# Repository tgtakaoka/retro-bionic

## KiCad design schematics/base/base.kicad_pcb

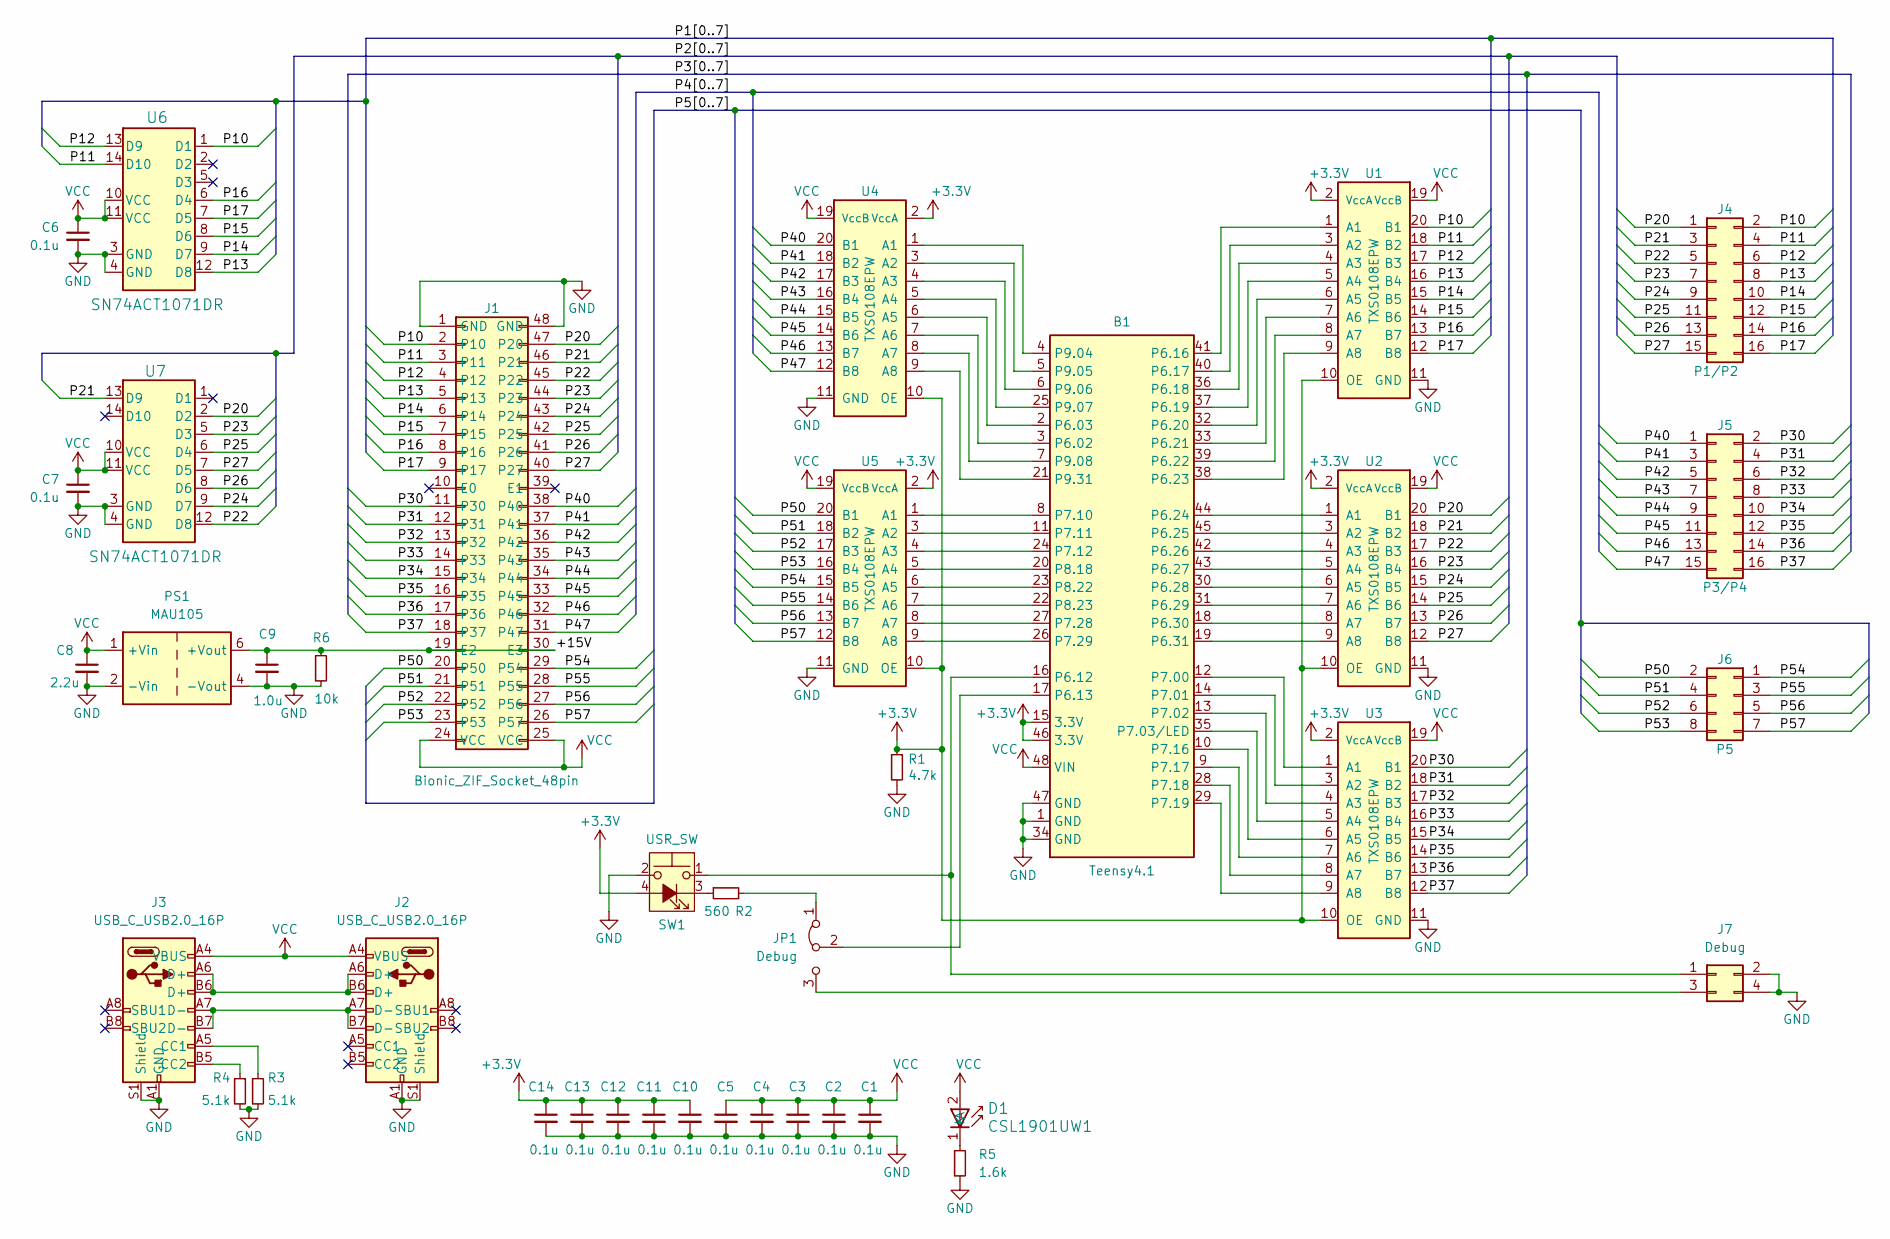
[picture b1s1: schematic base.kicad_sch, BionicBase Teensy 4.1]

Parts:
B1: Teensy4.1; Teensy 4.1
C1, C2, C3, C4, C5, C6, C7, C10, C11, C12, C13, C14: 0.1u; C_0603_1608Metric_Pad1.08x0.95mm_HandSolder
C8: 2.2u; C_0603_1608Metric_Pad1.08x0.95mm_HandSolder
C9: 1.0u; C_0603_1608Metric_Pad1.08x0.95mm_HandSolder
D1: CSL1901UW1; LED_CSL1901UW1_ROM-M
J1: Bionic_ZIF_Socket_48pin; Aries_ZIF_socket_DIP-48-pin
J2, J3: USB_C_USB2.0_16P; GCT_USB4085-GF-A_REVB
J4: P1/P2; PinHeader_2x08_P2.54mm_Horizontal
J5: P3/P4; PinHeader_2x08_P2.54mm_Horizontal
J6: P5; PinHeader_2x04_P2.54mm_Horizontal
J7: Debug; PinHeader_2x02_P2.54mm_Horizontal
JP1: Debug; PinHeader_1x03_P2.54mm_Vertical
PS1: MAU105; Converter_DCDC_Minmax_MAU100_THT
R1: 4.7k; R_0603_1608Metric_Pad0.98x0.95mm_HandSolder
R2: 560; R_0603_1608Metric_Pad0.98x0.95mm_HandSolder
R3, R4: 5.1k; R_0603_1608Metric_Pad0.98x0.95mm_HandSolder
R5: 1.6k; R_0603_1608Metric_Pad0.98x0.95mm_HandSolder
R6: 10k; R_0603_1608Metric_Pad0.98x0.95mm_HandSolder
SW1: USR_SW; SW_PUSH_LED_6mm
U1, U2, U3, U4, U5: TXS0108EPW; PW20-M
U6, U7: SN74ACT1071DR; D14-M

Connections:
+3.3V: B1.15 (3.3V), B1.46 (3.3V), C10.1, C11.1, C12.1, C13.1, C14.1, R1.1, SW1.4 (A), U1.2 (VccA), U1.10 (OE), U2.2 (VccA), U2.10 (OE), U3.2 (VccA), U3.10 (OE), U4.2 (VccA), U4.10 (OE), U5.2 (VccA), U5.10 (OE)
/+15V: C9.1, J1.19 (E2), J1.30 (E3), PS1.6 (+Vout), R6.1
/P10: J1.2 (P10), J4.2, U1.20 (B1), U6.1 (D1)
/P11: J1.3 (P11), J4.4, U1.18 (B2), U6.14 (D10)
/P12: J1.4 (P12), J4.6, U1.17 (B3), U6.13 (D9)
/P13: J1.5 (P13), J4.8, U1.16 (B4), U6.12 (D8)
/P14: J1.6 (P14), J4.10, U1.15 (B5), U6.9 (D7)
/P15: J1.7 (P15), J4.12, U1.14 (B6), U6.8 (D6)
/P16: J1.8 (P16), J4.14, U1.13 (B7), U6.6 (D4)
/P17: J1.9 (P17), J4.16, U1.12 (B8), U6.7 (D5)
/P20: J1.47 (P20), J4.1, U2.20 (B1), U7.2 (D2)
/P21: J1.46 (P21), J4.3, U2.18 (B2), U7.13 (D9)
/P22: J1.45 (P22), J4.5, U2.17 (B3), U7.12 (D8)
/P23: J1.44 (P23), J4.7, U2.16 (B4), U7.5 (D3)
/P24: J1.43 (P24), J4.9, U2.15 (B5), U7.9 (D7)
/P25: J1.42 (P25), J4.11, U2.14 (B6), U7.6 (D4)
/P26: J1.41 (P26), J4.13, U2.13 (B7), U7.8 (D6)
/P27: J1.40 (P27), J4.15, U2.12 (B8), U7.7 (D5)
/P30: J1.11 (P30), J5.2, U3.20 (B1)
/P31: J1.12 (P31), J5.4, U3.18 (B2)
/P32: J1.13 (P32), J5.6, U3.17 (B3)
/P33: J1.14 (P33), J5.8, U3.16 (B4)
/P34: J1.15 (P34), J5.10, U3.15 (B5)
/P35: J1.16 (P35), J5.12, U3.14 (B6)
/P36: J1.17 (P36), J5.14, U3.13 (B7)
/P37: J1.18 (P37), J5.16, U3.12 (B8)
/P40: J1.38 (P40), J5.1, U4.20 (B1)
/P41: J1.37 (P41), J5.3, U4.18 (B2)
/P42: J1.36 (P42), J5.5, U4.17 (B3)
/P43: J1.35 (P43), J5.7, U4.16 (B4)
/P44: J1.34 (P44), J5.9, U4.15 (B5)
/P45: J1.33 (P45), J5.11, U4.14 (B6)
/P46: J1.32 (P46), J5.13, U4.13 (B7)
/P47: J1.31 (P47), J5.15, U4.12 (B8)
/P50: J1.20 (P50), J6.2, U5.20 (B1)
/P51: J1.21 (P51), J6.4, U5.18 (B2)
/P52: J1.22 (P52), J6.6, U5.17 (B3)
/P53: J1.23 (P53), J6.8, U5.16 (B4)
/P54: J1.29 (P54), J6.1, U5.15 (B5)
/P55: J1.28 (P55), J6.3, U5.14 (B6)
/P56: J1.27 (P56), J6.5, U5.13 (B7)
/P57: J1.26 (P57), J6.7, U5.12 (B8)
GND: B1.1 (GND), B1.34 (GND), B1.47 (GND), C1.2, C2.2, C3.2, C4.2, C5.2, C6.2, C7.2, C8.2, C9.2, C10.2, C11.2, C12.2, C13.2, C14.2, J1.1 (GND), J1.48 (GND), J2.A1 (GND), J2.A12 (GND), J2.B1 (GND), J2.B12 (GND), J2.S1 (Shield), J2.S2 (Shield), J2.S3 (Shield), J2.S4 (Shield), J3.A1 (GND), J3.A12 (GND), J3.B1 (GND), J3.B12 (GND), J3.S1 (Shield), J3.S2 (Shield), J3.S3 (Shield), J3.S4 (Shield), J7.2, J7.4, PS1.2 (-Vin), PS1.4 (-Vout), R1.2, R3.2, R4.2, R5.2, R6.2, SW1.2, U1.11 (GND), U2.11 (GND), U3.11 (GND), U4.11 (GND), U5.11 (GND), U6.3 (GND), U6.4 (GND), U7.3 (GND), U7.4 (GND)
unnamed: B1.3 (P6.02), U4.7 (A6)
unnamed: B1.2 (P6.03), U4.6 (A5)
unnamed: B1.16 (P6.12), J7.1, SW1.1
unnamed: B1.17 (P6.13), JP1.2 (C)
unnamed: B1.41 (P6.16), U1.1 (A1)
unnamed: B1.40 (P6.17), U1.3 (A2)
unnamed: B1.36 (P6.18), U1.4 (A3)
unnamed: B1.37 (P6.19), U1.5 (A4)
unnamed: B1.32 (P6.20), U1.6 (A5)
unnamed: B1.33 (P6.21), U1.7 (A6)
unnamed: B1.39 (P6.22), U1.8 (A7)
unnamed: B1.38 (P6.23), U1.9 (A8)
unnamed: B1.44 (P6.24), U2.1 (A1)
unnamed: B1.45 (P6.25), U2.3 (A2)
unnamed: B1.42 (P6.26), U2.4 (A3)
unnamed: B1.43 (P6.27), U2.5 (A4)
unnamed: B1.30 (P6.28), U2.6 (A5)
unnamed: B1.31 (P6.29), U2.7 (A6)
unnamed: B1.18 (P6.30), U2.8 (A7)
unnamed: B1.19 (P6.31), U2.9 (A8)
unnamed: B1.12 (P7.00), U3.1 (A1)
unnamed: B1.14 (P7.01), U3.3 (A2)
unnamed: B1.13 (P7.02), U3.4 (A3)
unnamed: B1.35 (P7.03/LED), U3.5 (A4)
unnamed: B1.8 (P7.10), U5.1 (A1)
unnamed: B1.11 (P7.11), U5.3 (A2)
unnamed: B1.24 (P7.12), U5.4 (A3)
unnamed: B1.10 (P7.16), U3.6 (A5)
unnamed: B1.9 (P7.17), U3.7 (A6)
unnamed: B1.28 (P7.18), U3.8 (A7)
unnamed: B1.29 (P7.19), U3.9 (A8)
unnamed: B1.27 (P7.28), U5.8 (A7)
unnamed: B1.26 (P7.29), U5.9 (A8)
unnamed: B1.20 (P8.18), U5.5 (A4)
unnamed: B1.23 (P8.22), U5.6 (A5)
unnamed: B1.22 (P8.23), U5.7 (A6)
unnamed: B1.4 (P9.04), U4.1 (A1)
unnamed: B1.5 (P9.05), U4.3 (A2)
unnamed: B1.6 (P9.06), U4.4 (A3)
unnamed: B1.25 (P9.07), U4.5 (A4)
unnamed: B1.7 (P9.08), U4.8 (A7)
unnamed: B1.21 (P9.31), U4.9 (A8)
unnamed: D1.1 (K), R5.1
unnamed: J2.A6 (D+), J2.B6 (D+), J3.A6 (D+), J3.B6 (D+)
unnamed: J2.A7 (D-), J2.B7 (D-), J3.A7 (D-), J3.B7 (D-)
unnamed: J3.A5 (CC1), R3.1
unnamed: J3.B5 (CC2), R4.1
unnamed: J7.3, JP1.3 (B)
unnamed: JP1.1 (A), R2.2
unnamed: R2.1, SW1.3 (K)
VCC: B1.48 (VIN), C1.1, C2.1, C3.1, C4.1, C5.1, C6.1, C7.1, C8.1, D1.2 (A), J1.24 (VCC), J1.25 (VCC), J2.A4 (VBUS), J2.A9 (VBUS), J2.B4 (VBUS), J2.B9 (VBUS), J3.A4 (VBUS), J3.A9 (VBUS), J3.B4 (VBUS), J3.B9 (VBUS), PS1.1 (+Vin), U1.19 (VccB), U2.19 (VccB), U3.19 (VccB), U4.19 (VccB), U5.19 (VccB), U6.10 (VCC), U6.11 (VCC), U7.10 (VCC), U7.11 (VCC)

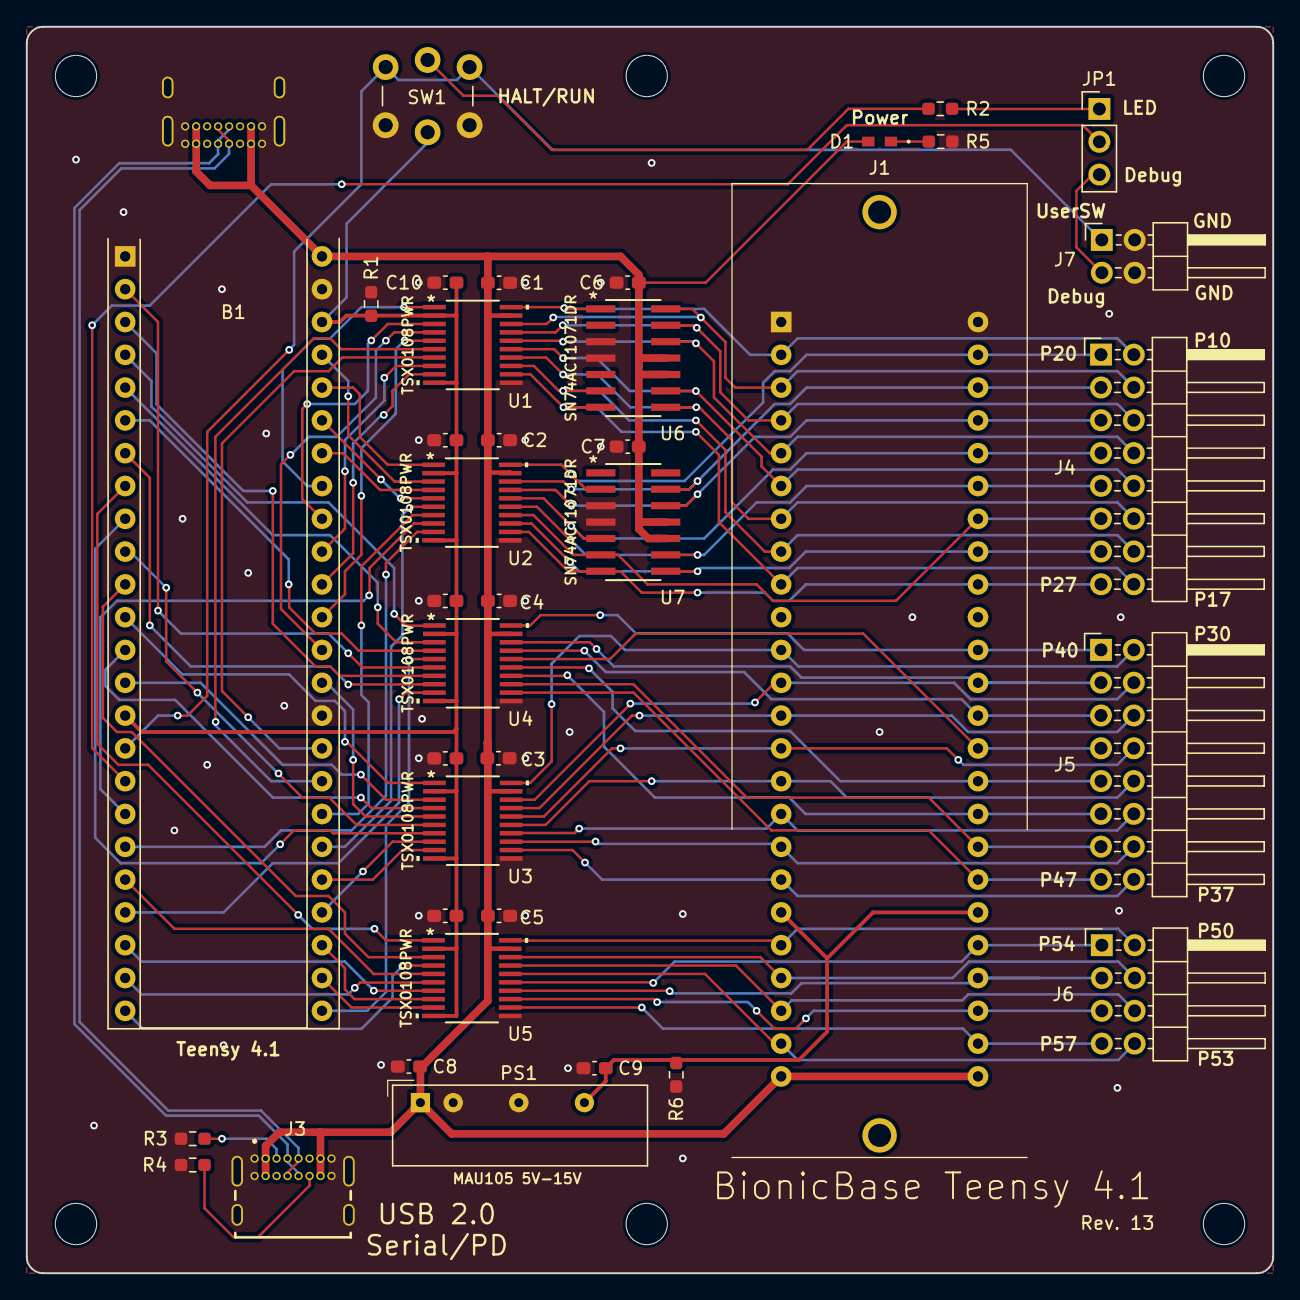
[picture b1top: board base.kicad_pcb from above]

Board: 2 copper layers, 96.5 x 96.5 mm, 45 parts (1 on the bottom side), 94 nets.

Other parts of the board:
MH1, MH2, MH3, MH4, MH5, MH6: MountingHole_3.2mm_M3

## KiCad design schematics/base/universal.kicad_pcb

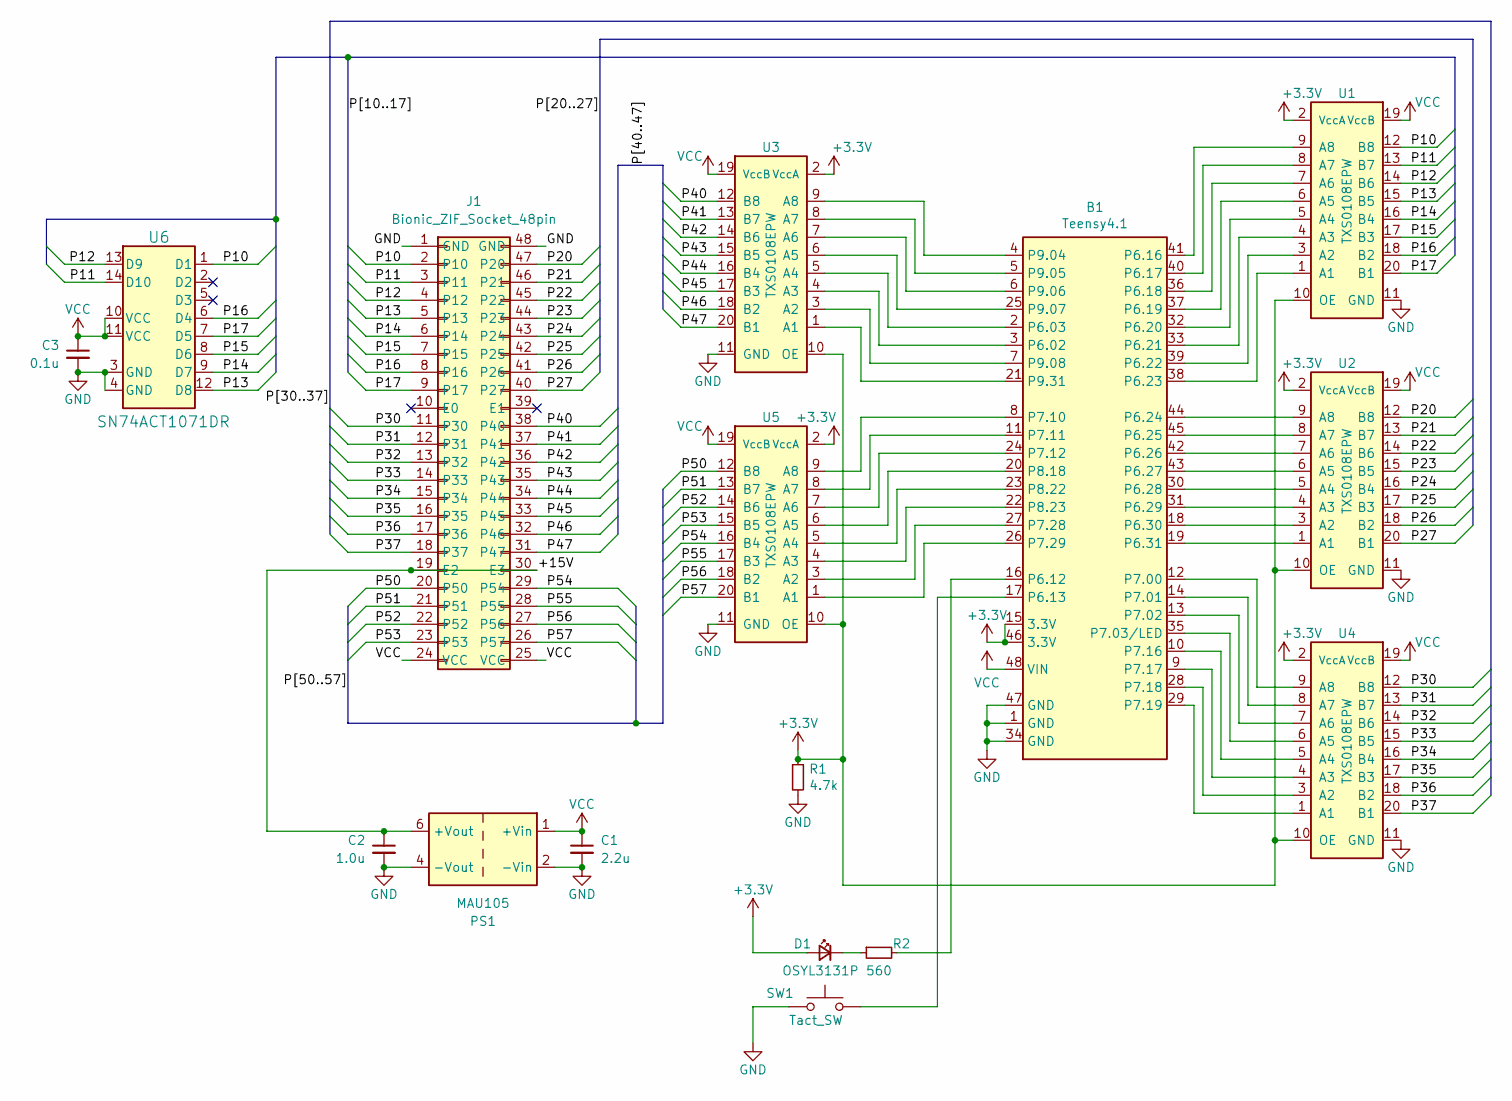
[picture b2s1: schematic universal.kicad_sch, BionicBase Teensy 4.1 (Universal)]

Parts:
B1: Teensy4.1; DIP-48_W15.24mm_Socket
C1: 2.2u; C_Disc_D3.4mm_W2.1mm_P2.50mm
C2: 1.0u; C_Disc_D3.4mm_W2.1mm_P2.50mm
C3: 0.1u; C_Disc_D3.4mm_W2.1mm_P2.50mm
D1: OSYL3131P; LED_D3.0mm
J1: Bionic_ZIF_Socket_48pin; Aries_ZIF_socket_DIP-48-pin
PS1: MAU105; Converter_DCDC_Minmax_MAU100_THT
R1: 4.7k; R_Axial_DIN0204_L3.6mm_D1.6mm_P5.08mm_Horizontal
R2: 560; R_Axial_DIN0204_L3.6mm_D1.6mm_P5.08mm_Horizontal
SW1: Tact_SW; Tact_SW_6x6mm
U1, U2, U3, U4, U5: TXS0108EPW; DIP-20_W12.70mm_Socket
U6: SN74ACT1071DR; DIP-14_W15.24mm_Socket

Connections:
+3.3V: B1.15 (3.3V), B1.46 (3.3V), D1.2 (A), R1.1, U1.2 (VccA), U1.10 (OE), U2.2 (VccA), U2.10 (OE), U3.2 (VccA), U3.10 (OE), U4.2 (VccA), U4.10 (OE), U5.2 (VccA), U5.10 (OE)
/+15V: C2.1, J1.19 (E2), J1.30 (E3), PS1.6 (+Vout)
/P10: J1.2 (P10), U1.12 (B8), U6.1 (D1)
/P11: J1.3 (P11), U1.13 (B7), U6.14 (D10)
/P12: J1.4 (P12), U1.14 (B6), U6.13 (D9)
/P13: J1.5 (P13), U1.15 (B5), U6.12 (D8)
/P14: J1.6 (P14), U1.16 (B4), U6.9 (D7)
/P15: J1.7 (P15), U1.17 (B3), U6.8 (D6)
/P16: J1.8 (P16), U1.18 (B2), U6.6 (D4)
/P17: J1.9 (P17), U1.20 (B1), U6.7 (D5)
/P20: J1.47 (P20), U2.12 (B8)
/P21: J1.46 (P21), U2.13 (B7)
/P22: J1.45 (P22), U2.14 (B6)
/P23: J1.44 (P23), U2.15 (B5)
/P24: J1.43 (P24), U2.16 (B4)
/P25: J1.42 (P25), U2.17 (B3)
/P26: J1.41 (P26), U2.18 (B2)
/P27: J1.40 (P27), U2.20 (B1)
/P30: J1.11 (P30), U4.12 (B8)
/P31: J1.12 (P31), U4.13 (B7)
/P32: J1.13 (P32), U4.14 (B6)
/P33: J1.14 (P33), U4.15 (B5)
/P34: J1.15 (P34), U4.16 (B4)
/P35: J1.16 (P35), U4.17 (B3)
/P36: J1.17 (P36), U4.18 (B2)
/P37: J1.18 (P37), U4.20 (B1)
/P40: J1.38 (P40), U3.12 (B8)
/P41: J1.37 (P41), U3.13 (B7)
/P42: J1.36 (P42), U3.14 (B6)
/P43: J1.35 (P43), U3.15 (B5)
/P44: J1.34 (P44), U3.16 (B4)
/P45: J1.33 (P45), U3.17 (B3)
/P46: J1.32 (P46), U3.18 (B2)
/P47: J1.31 (P47), U3.20 (B1)
/P50: J1.20 (P50), U5.12 (B8)
/P51: J1.21 (P51), U5.13 (B7)
/P52: J1.22 (P52), U5.14 (B6)
/P53: J1.23 (P53), U5.15 (B5)
/P54: J1.29 (P54), U5.16 (B4)
/P55: J1.28 (P55), U5.17 (B3)
/P56: J1.27 (P56), U5.18 (B2)
/P57: J1.26 (P57), U5.20 (B1)
GND: B1.1 (GND), B1.34 (GND), B1.47 (GND), C1.2, C2.2, C3.2, J1.1 (GND), J1.48 (GND), PS1.2 (-Vin), PS1.4 (-Vout), R1.2, SW1.2, U1.11 (GND), U2.11 (GND), U3.11 (GND), U4.11 (GND), U5.11 (GND), U6.3 (GND), U6.4 (GND)
unnamed: B1.3 (P6.02), U3.4 (A3)
unnamed: B1.2 (P6.03), U3.5 (A4)
unnamed: B1.16 (P6.12), R2.2
unnamed: B1.17 (P6.13), SW1.1
unnamed: B1.41 (P6.16), U1.9 (A8)
unnamed: B1.40 (P6.17), U1.8 (A7)
unnamed: B1.36 (P6.18), U1.7 (A6)
unnamed: B1.37 (P6.19), U1.6 (A5)
unnamed: B1.32 (P6.20), U1.5 (A4)
unnamed: B1.33 (P6.21), U1.4 (A3)
unnamed: B1.39 (P6.22), U1.3 (A2)
unnamed: B1.38 (P6.23), U1.1 (A1)
unnamed: B1.44 (P6.24), U2.9 (A8)
unnamed: B1.45 (P6.25), U2.8 (A7)
unnamed: B1.42 (P6.26), U2.7 (A6)
unnamed: B1.43 (P6.27), U2.6 (A5)
unnamed: B1.30 (P6.28), U2.5 (A4)
unnamed: B1.31 (P6.29), U2.4 (A3)
unnamed: B1.18 (P6.30), U2.3 (A2)
unnamed: B1.19 (P6.31), U2.1 (A1)
unnamed: B1.12 (P7.00), U4.9 (A8)
unnamed: B1.14 (P7.01), U4.8 (A7)
unnamed: B1.13 (P7.02), U4.7 (A6)
unnamed: B1.35 (P7.03/LED), U4.6 (A5)
unnamed: B1.8 (P7.10), U5.9 (A8)
unnamed: B1.11 (P7.11), U5.8 (A7)
unnamed: B1.24 (P7.12), U5.7 (A6)
unnamed: B1.10 (P7.16), U4.5 (A4)
unnamed: B1.9 (P7.17), U4.4 (A3)
unnamed: B1.28 (P7.18), U4.3 (A2)
unnamed: B1.29 (P7.19), U4.1 (A1)
unnamed: B1.27 (P7.28), U5.3 (A2)
unnamed: B1.26 (P7.29), U5.1 (A1)
unnamed: B1.20 (P8.18), U5.6 (A5)
unnamed: B1.23 (P8.22), U5.5 (A4)
unnamed: B1.22 (P8.23), U5.4 (A3)
unnamed: B1.4 (P9.04), U3.9 (A8)
unnamed: B1.5 (P9.05), U3.8 (A7)
unnamed: B1.6 (P9.06), U3.7 (A6)
unnamed: B1.25 (P9.07), U3.6 (A5)
unnamed: B1.7 (P9.08), U3.3 (A2)
unnamed: B1.21 (P9.31), U3.1 (A1)
unnamed: D1.1 (K), R2.1
VCC: B1.48 (VIN), C1.1, C3.1, J1.24 (VCC), J1.25 (VCC), PS1.1 (+Vin), U1.19 (VccB), U2.19 (VccB), U3.19 (VccB), U4.19 (VccB), U5.19 (VccB), U6.10 (VCC), U6.11 (VCC)

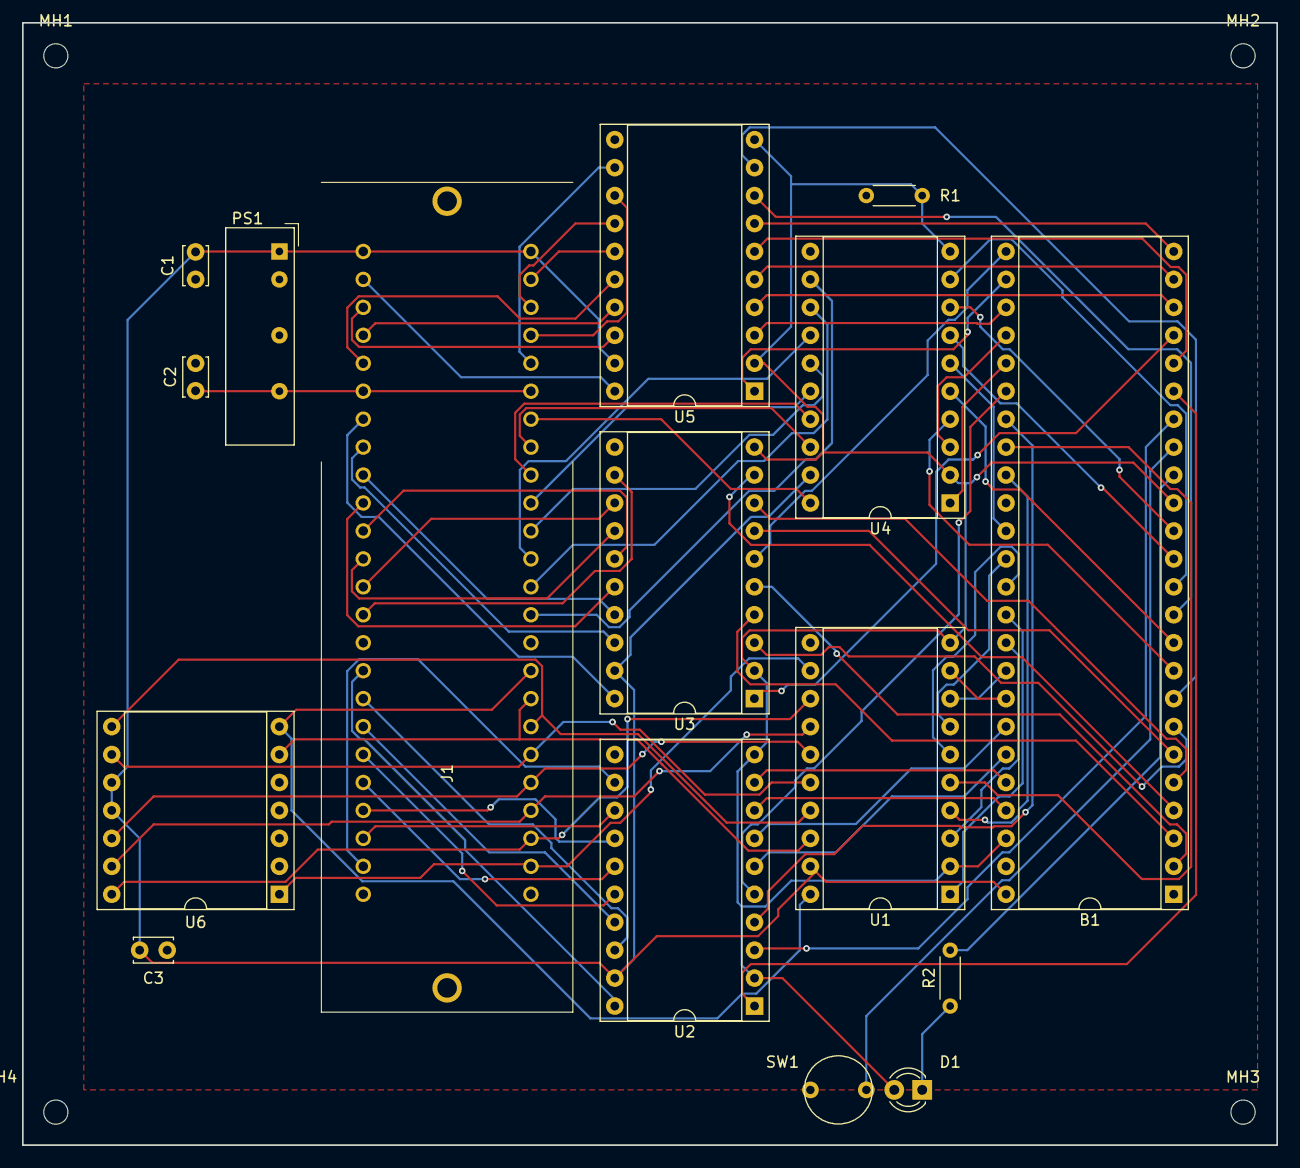
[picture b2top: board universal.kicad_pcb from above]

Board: 2 copper layers, 114.0 x 102.0 mm, 20 parts (0 on the bottom side), 87 nets.

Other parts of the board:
MH1, MH2, MH3, MH4: MountingHole_2.2mm_M2

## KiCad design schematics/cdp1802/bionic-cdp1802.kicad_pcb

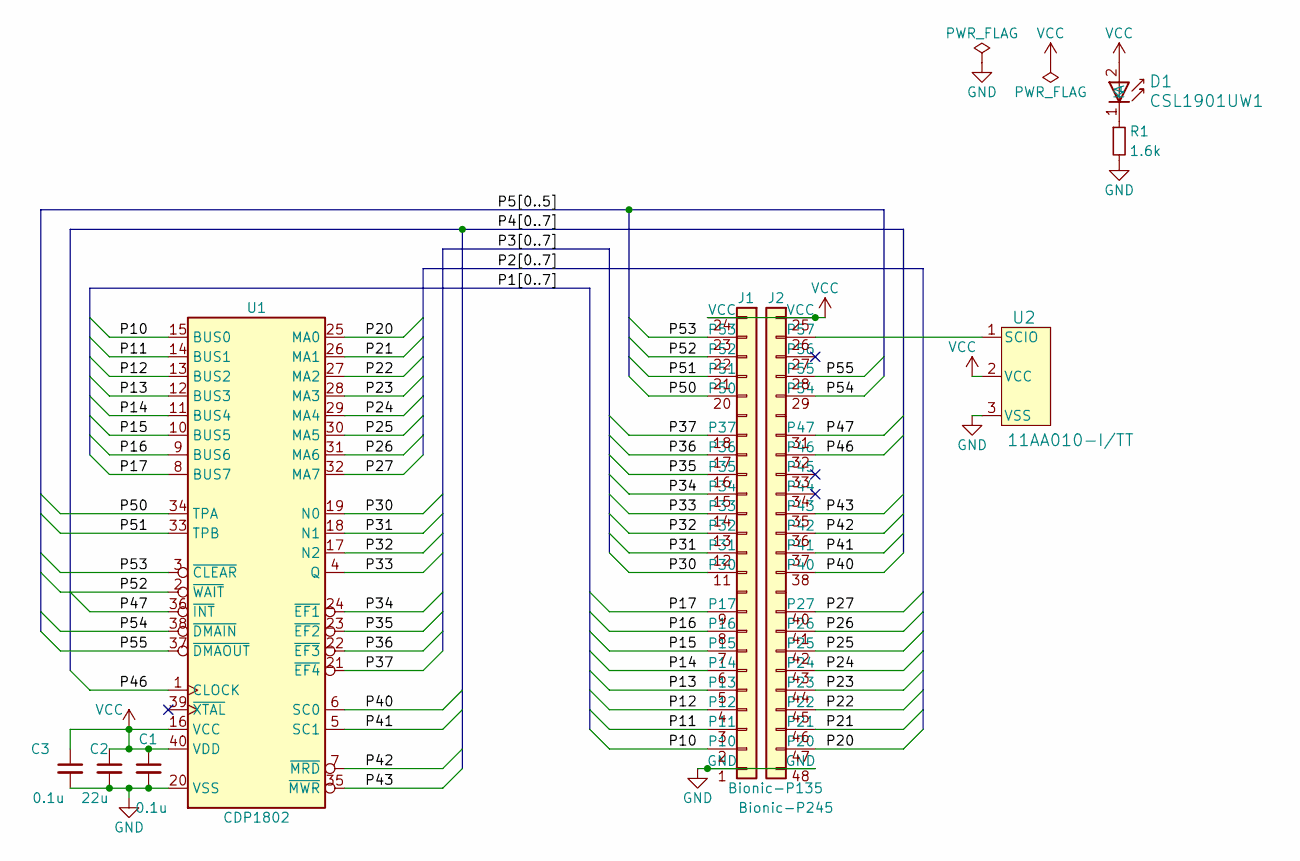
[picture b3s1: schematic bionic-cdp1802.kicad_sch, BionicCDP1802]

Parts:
C1, C3: 0.1u; C_0603_1608Metric_Pad1.08x0.95mm_HandSolder
C2: 22u; C_0603_1608Metric_Pad1.08x0.95mm_HandSolder
D1: CSL1901UW1; LED_CSL1901UW1_ROM-M
J1: Bionic-P135; Bionic-P135_THT
J2: Bionic-P245; Bionic-P245_THT
R1: 1.6k; R_0603_1608Metric_Pad0.98x0.95mm_HandSolder
U1: CDP1802; DIP-40_W15.24mm_Socket
U2: 11AA010-I/TT; SOT-23_MC_MCH-M

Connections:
/P10: J1.2 (P10), U1.15 (BUS0)
/P11: J1.3 (P11), U1.14 (BUS1)
/P12: J1.4 (P12), U1.13 (BUS2)
/P13: J1.5 (P13), U1.12 (BUS3)
/P14: J1.6 (P14), U1.11 (BUS4)
/P15: J1.7 (P15), U1.10 (BUS5)
/P16: J1.8 (P16), U1.9 (BUS6)
/P17: J1.9 (P17), U1.8 (BUS7)
/P20: J2.47 (P20), U1.25 (MA0)
/P21: J2.46 (P21), U1.26 (MA1)
/P22: J2.45 (P22), U1.27 (MA2)
/P23: J2.44 (P23), U1.28 (MA3)
/P24: J2.43 (P24), U1.29 (MA4)
/P25: J2.42 (P25), U1.30 (MA5)
/P26: J2.41 (P26), U1.31 (MA6)
/P27: J2.40 (P27), U1.32 (MA7)
/P30: J1.11 (P30), U1.19 (N0)
/P31: J1.12 (P31), U1.18 (N1)
/P32: J1.13 (P32), U1.17 (N2)
/P33: J1.14 (P33), U1.4 (Q)
/P34: J1.15 (P34), U1.24 (~EF1)
/P35: J1.16 (P35), U1.23 (~EF2)
/P36: J1.17 (P36), U1.22 (~EF3)
/P37: J1.18 (P37), U1.21 (~EF4)
/P40: J2.38 (P40), U1.6 (SC0)
/P41: J2.37 (P41), U1.5 (SC1)
/P42: J2.36 (P42), U1.7 (~MRD)
/P43: J2.35 (P43), U1.35 (~MWR)
/P46: J2.32 (P46), U1.1 (CLOCK)
/P47: J2.31 (P47), U1.36 (~INT)
/P50: J1.20 (P50), U1.34 (TPA)
/P51: J1.21 (P51), U1.33 (TPB)
/P52: J1.22 (P52), U1.2 (~WAIT)
/P53: J1.23 (P53), U1.3 (~CLEAR)
/P54: J2.29 (P54), U1.38 (~DMAIN)
/P55: J2.28 (P55), U1.37 (~DMAOUT)
GND: C1.2, C2.2, C3.2, J1.1 (GND), J2.48 (GND), R1.2, U1.20 (VSS), U2.3 (VSS)
unnamed: D1.1 (K), R1.1
unnamed: J2.26 (P57), U2.1 (SCIO)
VCC: C1.1, C2.1, C3.1, D1.2 (A), J1.24 (VCC), J2.25 (VCC), U1.16 (VCC), U1.40 (VDD), U2.2 (VCC)

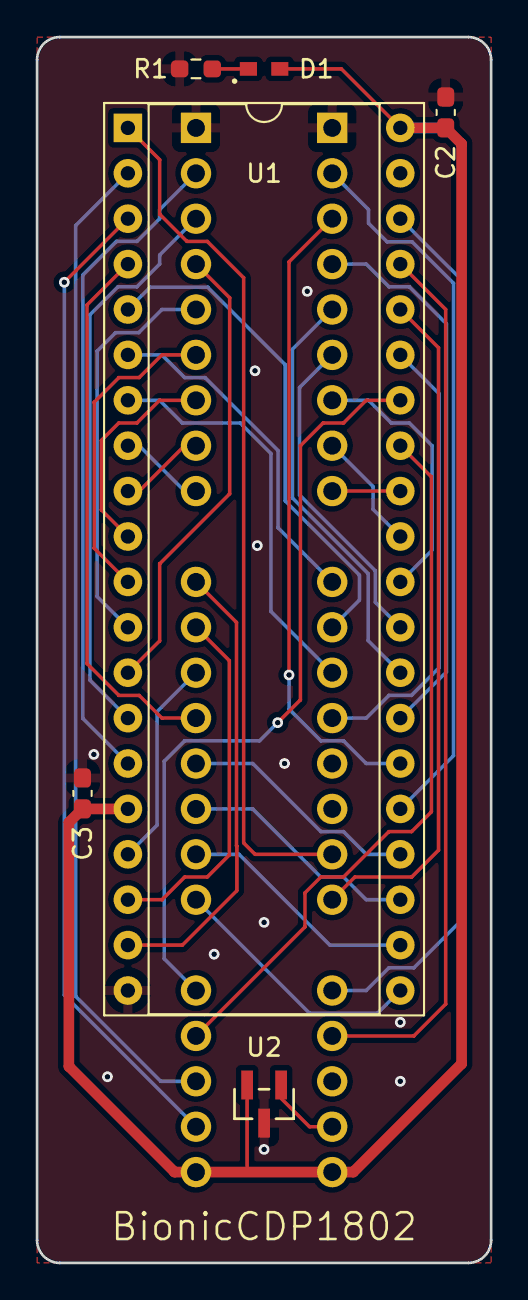
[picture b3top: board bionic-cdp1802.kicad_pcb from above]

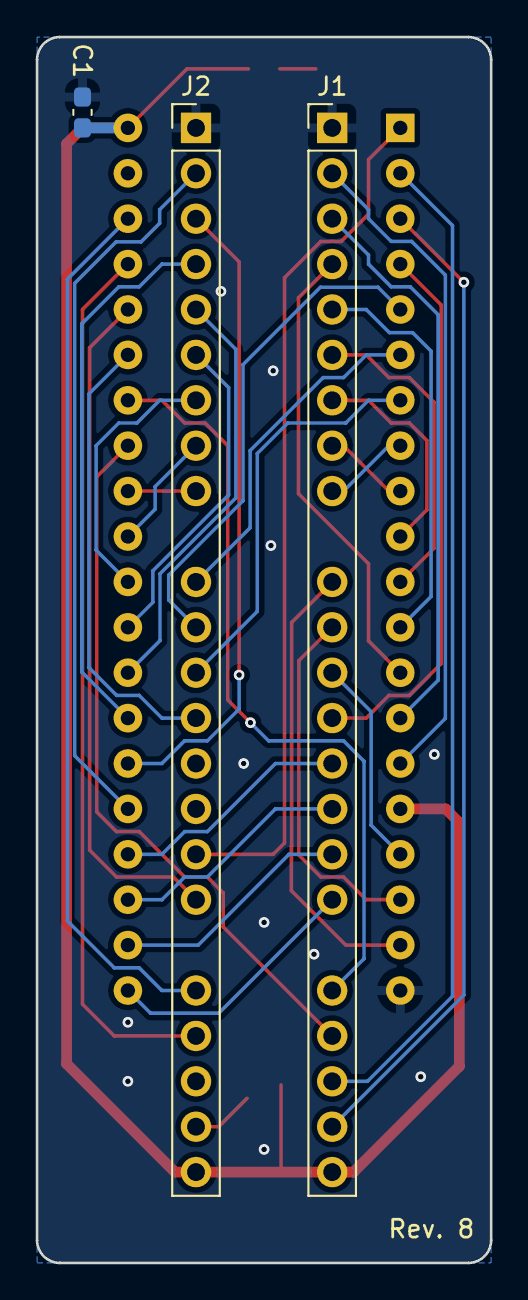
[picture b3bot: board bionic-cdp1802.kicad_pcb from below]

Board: 2 copper layers, 25.4 x 68.6 mm, 9 parts (3 on the bottom side), 40 nets.

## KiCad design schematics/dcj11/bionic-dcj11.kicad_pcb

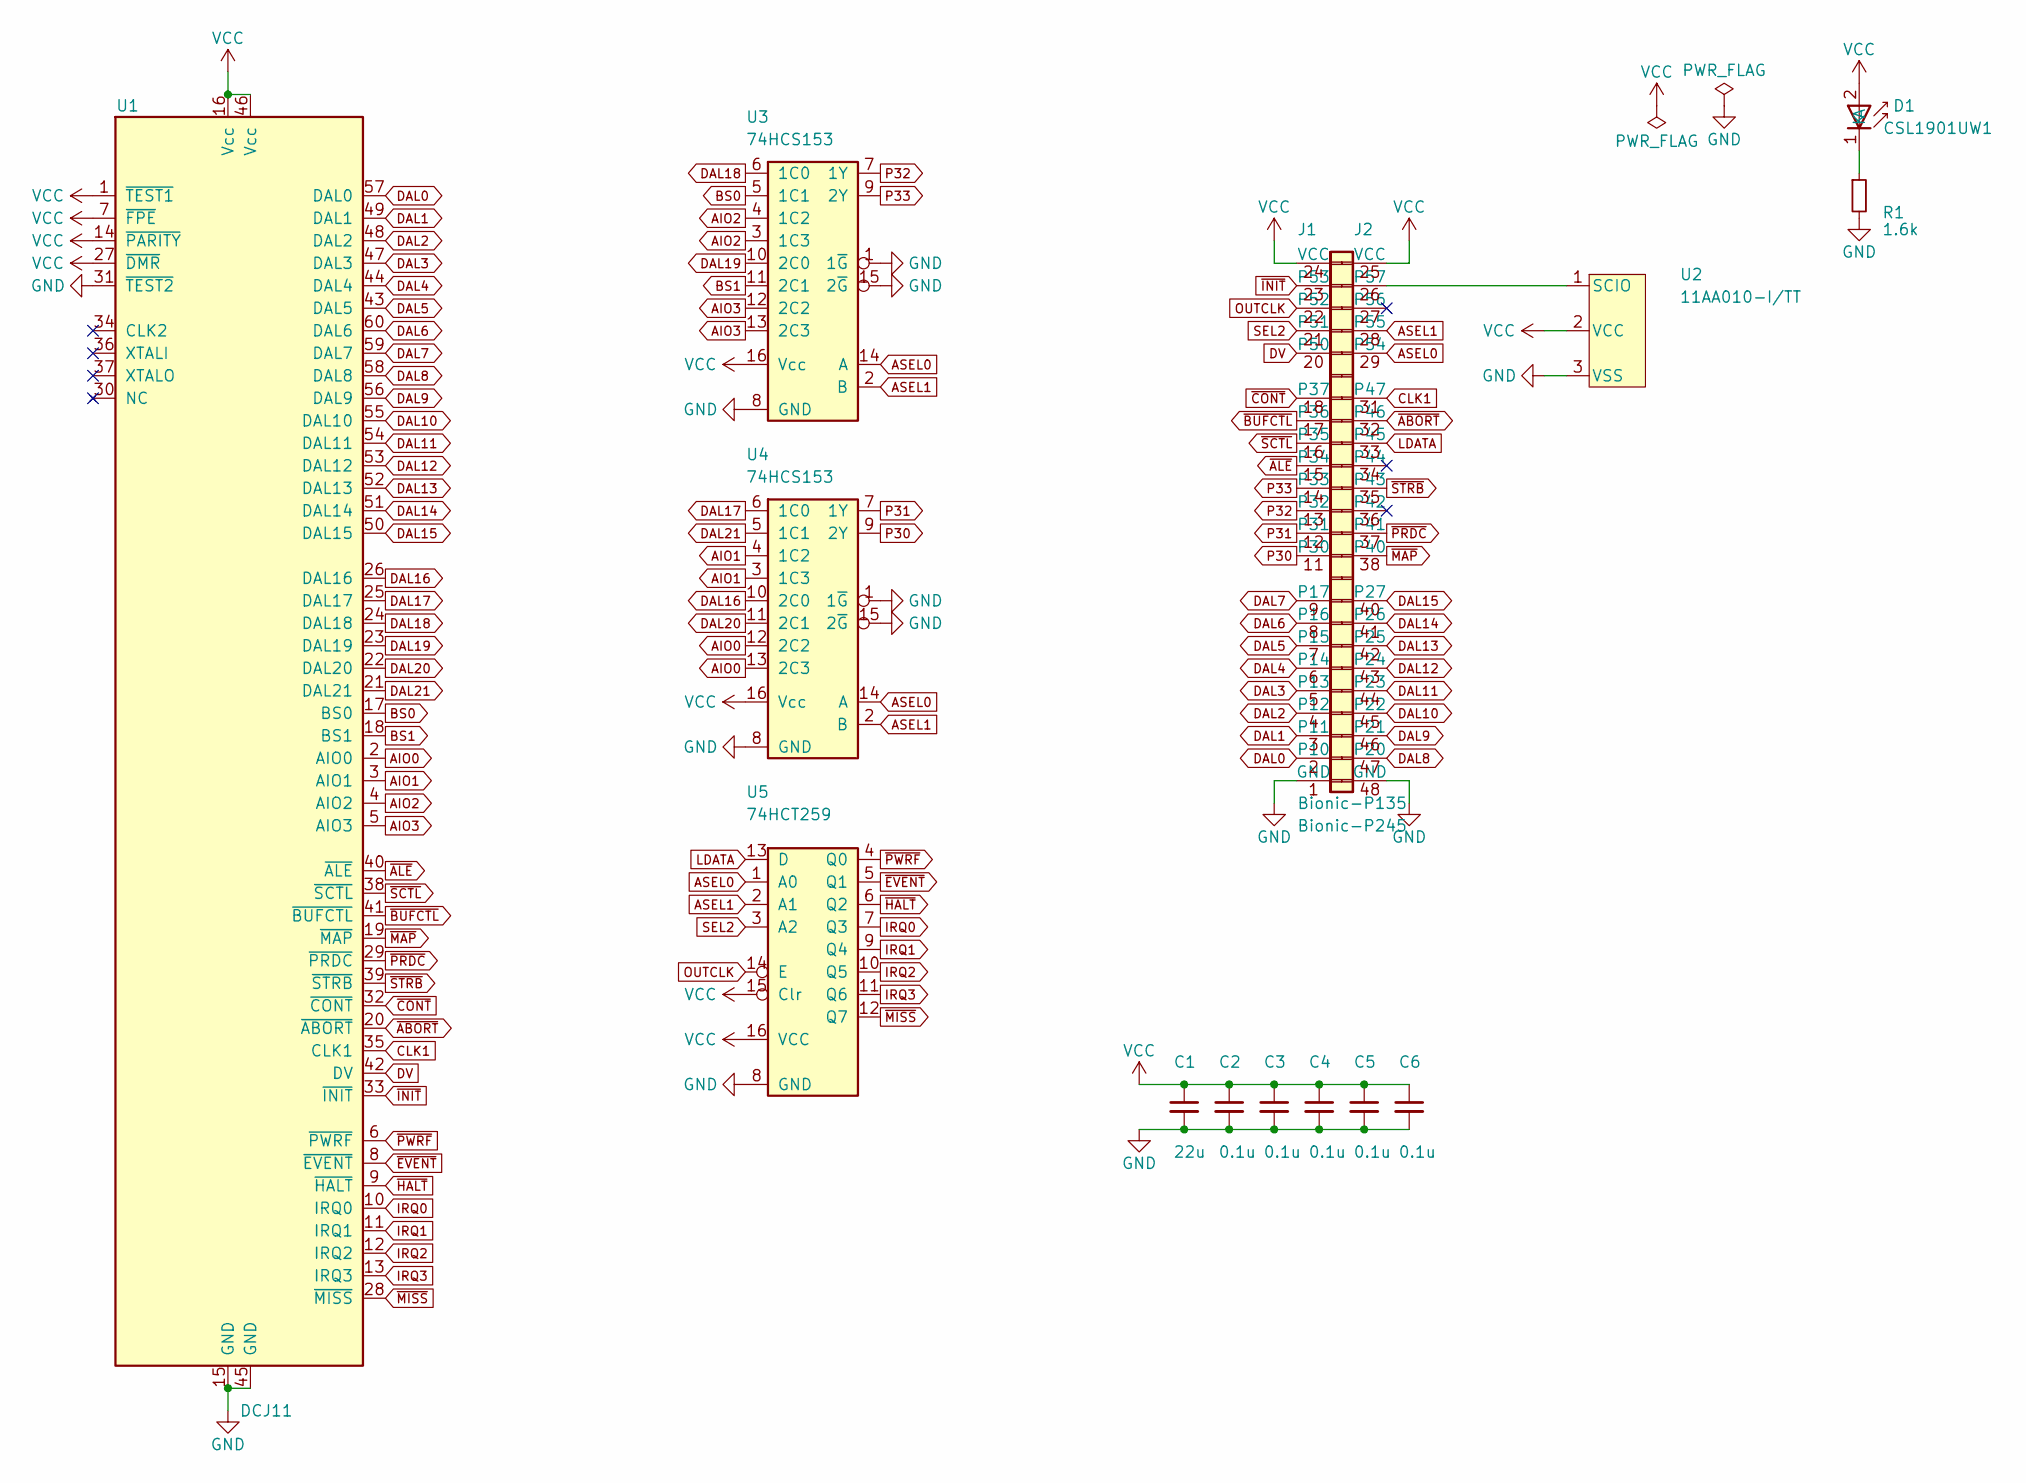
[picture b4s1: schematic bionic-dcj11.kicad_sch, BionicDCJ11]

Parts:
C1: 22u; C_0603_1608Metric_Pad1.08x0.95mm_HandSolder
C2, C3, C4, C5, C6: 0.1u; C_0603_1608Metric_Pad1.08x0.95mm_HandSolder
D1: CSL1901UW1; LED_CSL1901UW1_ROM-M
J1: Bionic-P135; Bionic-P135_THT
J2: Bionic-P245; Bionic-P245_THT
R1: 1.6k; R_0603_1608Metric_Pad0.98x0.95mm_HandSolder
U1: DCJ11; DIP-60_W33.02mm_Socket
U2: 11AA010-I/TT; SOT-23_MC_MCH-M
U3, U4: 74HCS153; PW16-M
U5: 74HCT259; TSSOP16_SOT403-1_NEX-M

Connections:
AIO0: U1.2 (AIO0), U4.12 (2C2), U4.13 (2C3)
AIO1: U1.3 (AIO1), U4.3 (1C3), U4.4 (1C2)
AIO2: U1.4 (AIO2), U3.3 (1C3), U3.4 (1C2)
AIO3: U1.5 (AIO3), U3.12 (2C2), U3.13 (2C3)
ASEL0: J2.29 (P54), U3.14 (A), U4.14 (A), U5.1 (A0)
ASEL1: J2.28 (P55), U3.2 (B), U4.2 (B), U5.2 (A1)
BS0: U1.17 (BS0), U3.5 (1C1)
BS1: U1.18 (BS1), U3.11 (2C1)
CLK1: J2.31 (P47), U1.35 (CLK1)
DAL0: J1.2 (P10), U1.57 (DAL0)
DAL1: J1.3 (P11), U1.49 (DAL1)
DAL2: J1.4 (P12), U1.48 (DAL2)
DAL3: J1.5 (P13), U1.47 (DAL3)
DAL4: J1.6 (P14), U1.44 (DAL4)
DAL5: J1.7 (P15), U1.43 (DAL5)
DAL6: J1.8 (P16), U1.60 (DAL6)
DAL7: J1.9 (P17), U1.59 (DAL7)
DAL8: J2.47 (P20), U1.58 (DAL8)
DAL9: J2.46 (P21), U1.56 (DAL9)
DAL10: J2.45 (P22), U1.55 (DAL10)
DAL11: J2.44 (P23), U1.54 (DAL11)
DAL12: J2.43 (P24), U1.53 (DAL12)
DAL13: J2.42 (P25), U1.52 (DAL13)
DAL14: J2.41 (P26), U1.51 (DAL14)
DAL15: J2.40 (P27), U1.50 (DAL15)
DAL16: U1.26 (DAL16), U4.10 (2C0)
DAL17: U1.25 (DAL17), U4.6 (1C0)
DAL18: U1.24 (DAL18), U3.6 (1C0)
DAL19: U1.23 (DAL19), U3.10 (2C0)
DAL20: U1.22 (DAL20), U4.11 (2C1)
DAL21: U1.21 (DAL21), U4.5 (1C1)
DV: J1.20 (P50), U1.42 (DV)
GND: C1.2, C2.2, C3.2, C4.2, C5.2, C6.2, J1.1 (GND), J2.48 (GND), R1.2, U1.15 (GND), U1.31 (~TEST2), U1.45 (GND), U2.3 (VSS), U3.1 (1~G), U3.8 (GND), U3.15 (2~G), U4.1 (1~G), U4.8 (GND), U4.15 (2~G), U5.8 (GND)
IRQ0: U1.10 (IRQ0), U5.7 (Q3)
IRQ1: U1.11 (IRQ1), U5.9 (Q4)
IRQ2: U1.12 (IRQ2), U5.10 (Q5)
IRQ3: U1.13 (IRQ3), U5.11 (Q6)
LDATA: J2.33 (P45), U5.13 (D)
unnamed: D1.1 (K), R1.1
unnamed: J2.26 (P57), U2.1 (SCIO)
OUTCLK: J1.22 (P52), U5.14 (E)
P30: J1.11 (P30), U4.9 (2Y)
P31: J1.12 (P31), U4.7 (1Y)
P32: J1.13 (P32), U3.7 (1Y)
P33: J1.14 (P33), U3.9 (2Y)
SEL2: J1.21 (P51), U5.3 (A2)
VCC: C1.1, C2.1, C3.1, C4.1, C5.1, C6.1, D1.2 (A), J1.24 (VCC), J2.25 (VCC), U1.1 (~TEST1), U1.7 (~FPE), U1.14 (~PARITY), U1.16 (Vcc), U1.27 (~DMR), U1.46 (Vcc), U2.2 (VCC), U3.16 (Vcc), U4.16 (Vcc), U5.15 (Clr), U5.16 (VCC)
~ABORT: J2.32 (P46), U1.20 (~ABORT)
~ALE: J1.15 (P34), U1.40 (~ALE)
~BUFCTL: J1.17 (P36), U1.41 (~BUFCTL)
~CONT: J1.18 (P37), U1.32 (~CONT)
~EVENT: U1.8 (~EVENT), U5.5 (Q1)
~HALT: U1.9 (~HALT), U5.6 (Q2)
~INIT: J1.23 (P53), U1.33 (~INIT)
~MAP: J2.38 (P40), U1.19 (~MAP)
~MISS: U1.28 (~MISS), U5.12 (Q7)
~PRDC: J2.37 (P41), U1.29 (~PRDC)
~PWRF: U1.6 (~PWRF), U5.4 (Q0)
~SCTL: J1.16 (P35), U1.38 (~SCTL)
~STRB: J2.35 (P43), U1.39 (~STRB)
